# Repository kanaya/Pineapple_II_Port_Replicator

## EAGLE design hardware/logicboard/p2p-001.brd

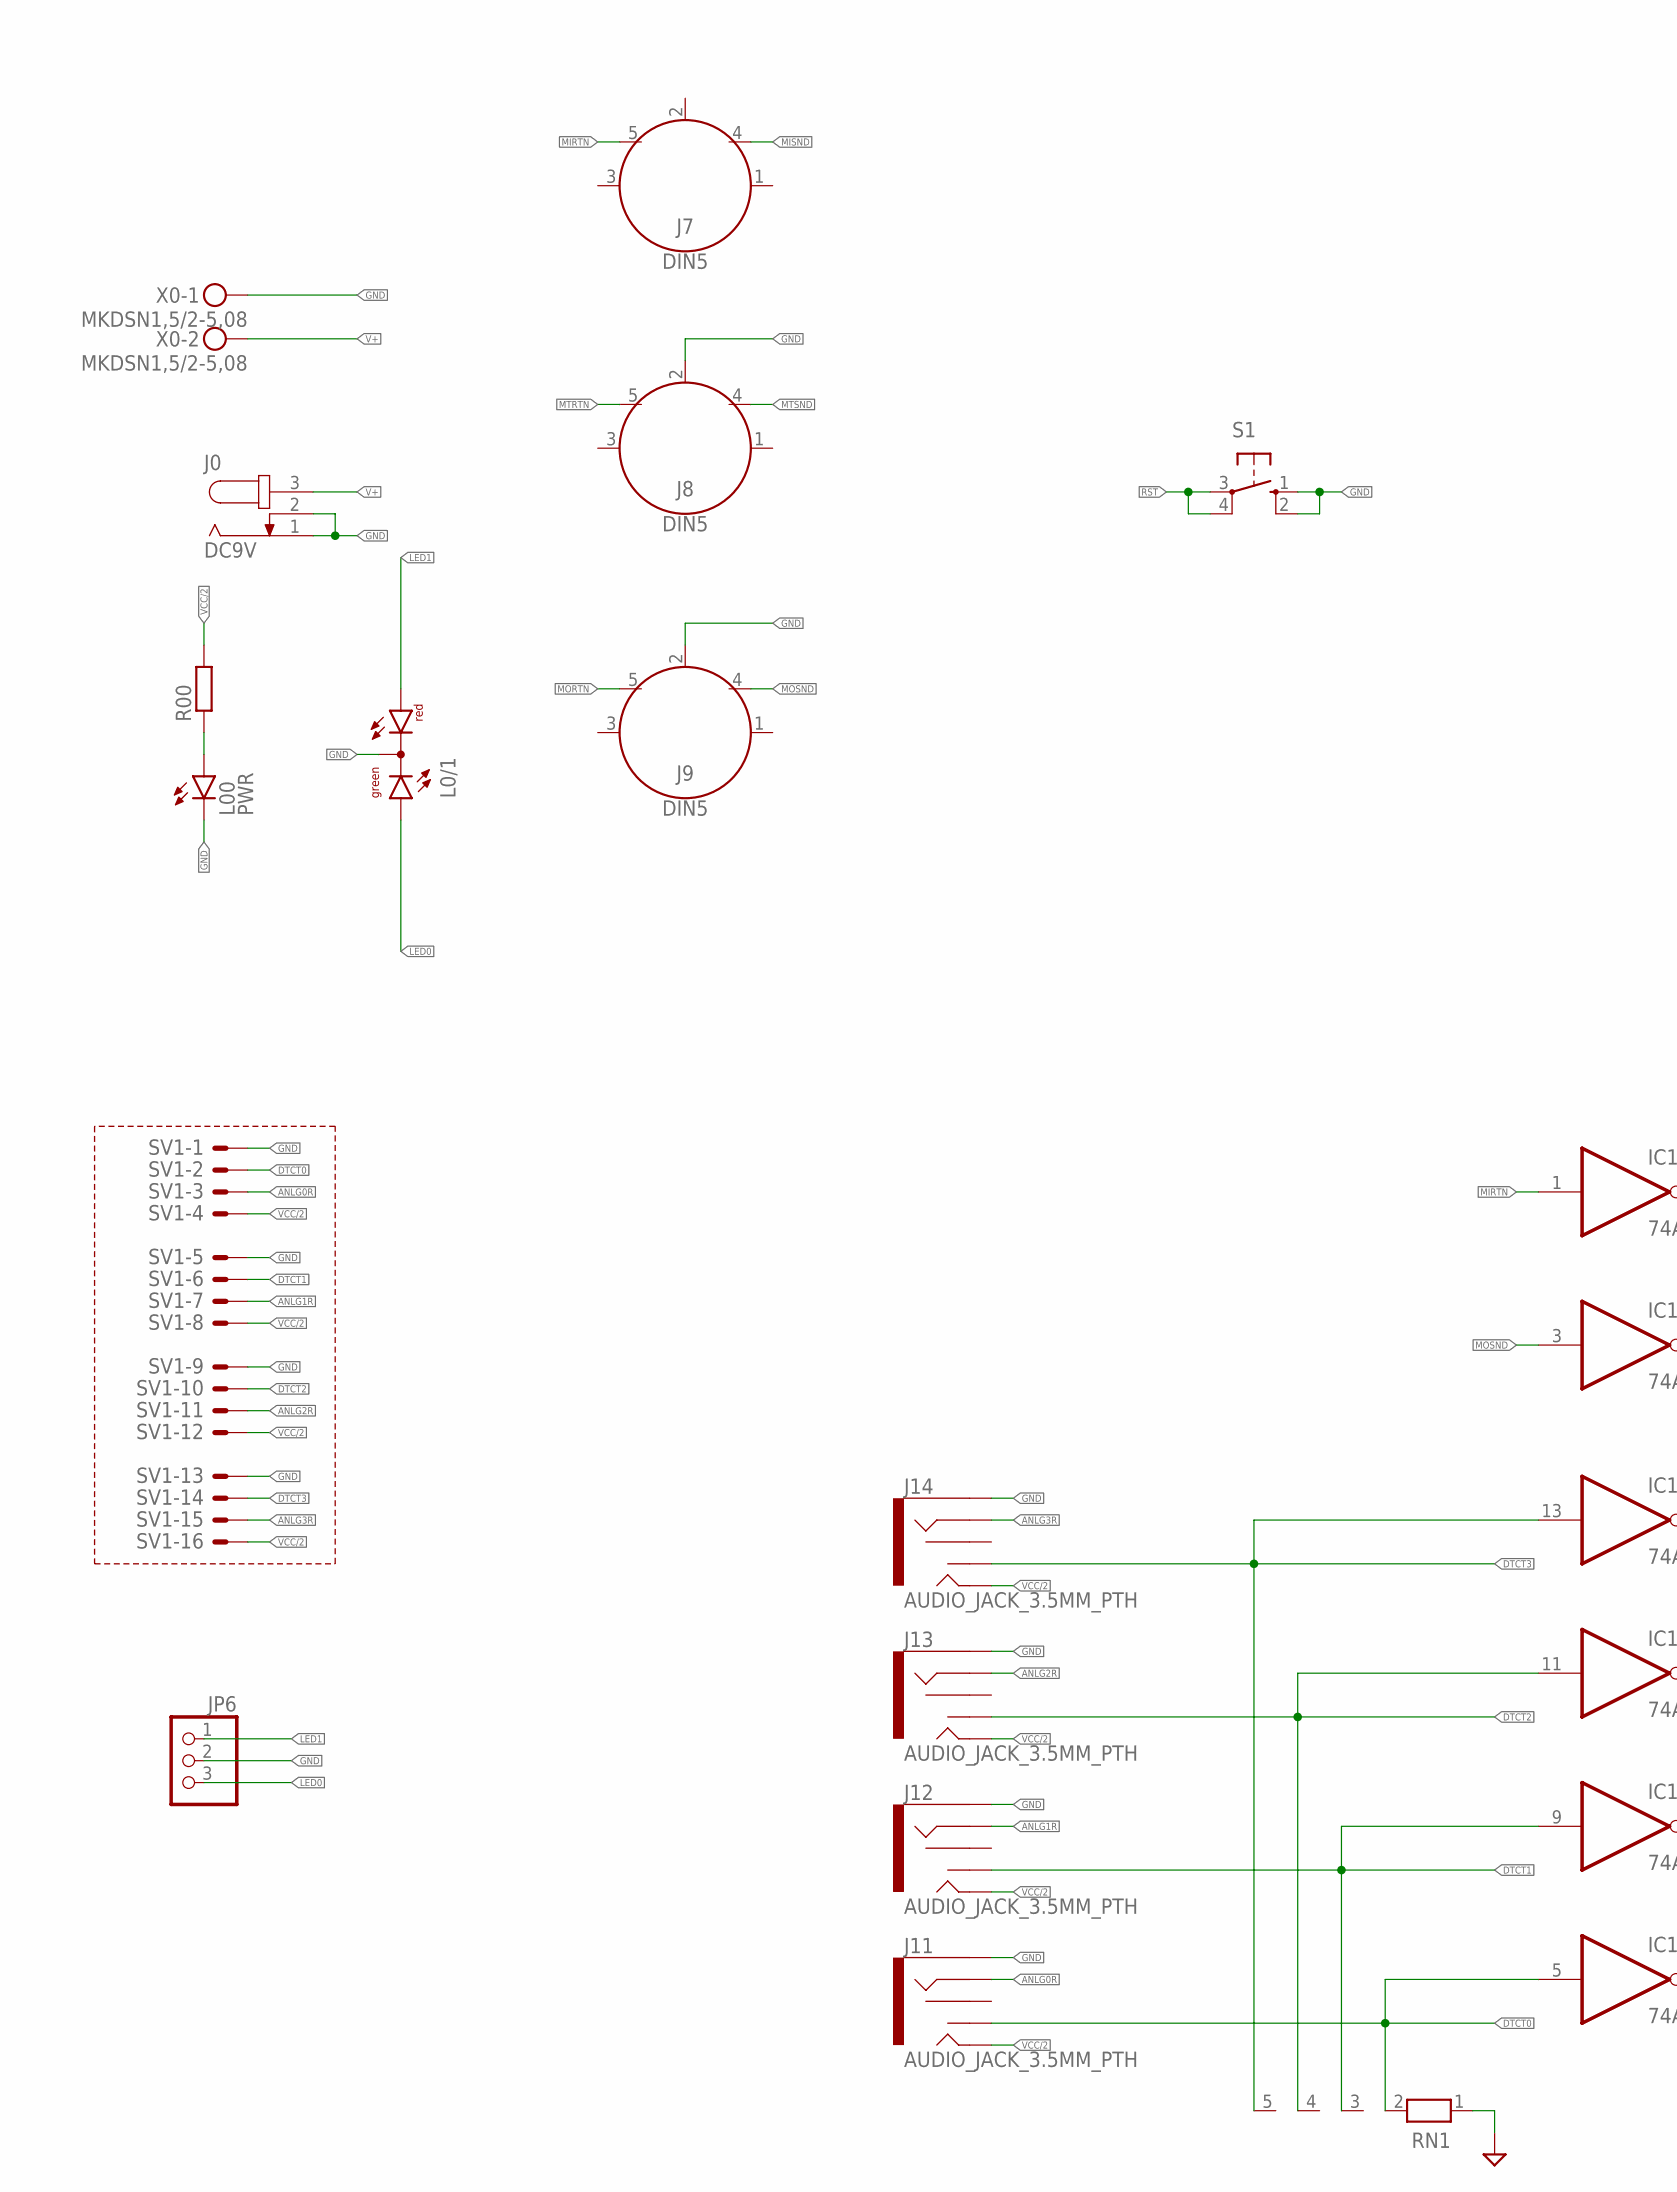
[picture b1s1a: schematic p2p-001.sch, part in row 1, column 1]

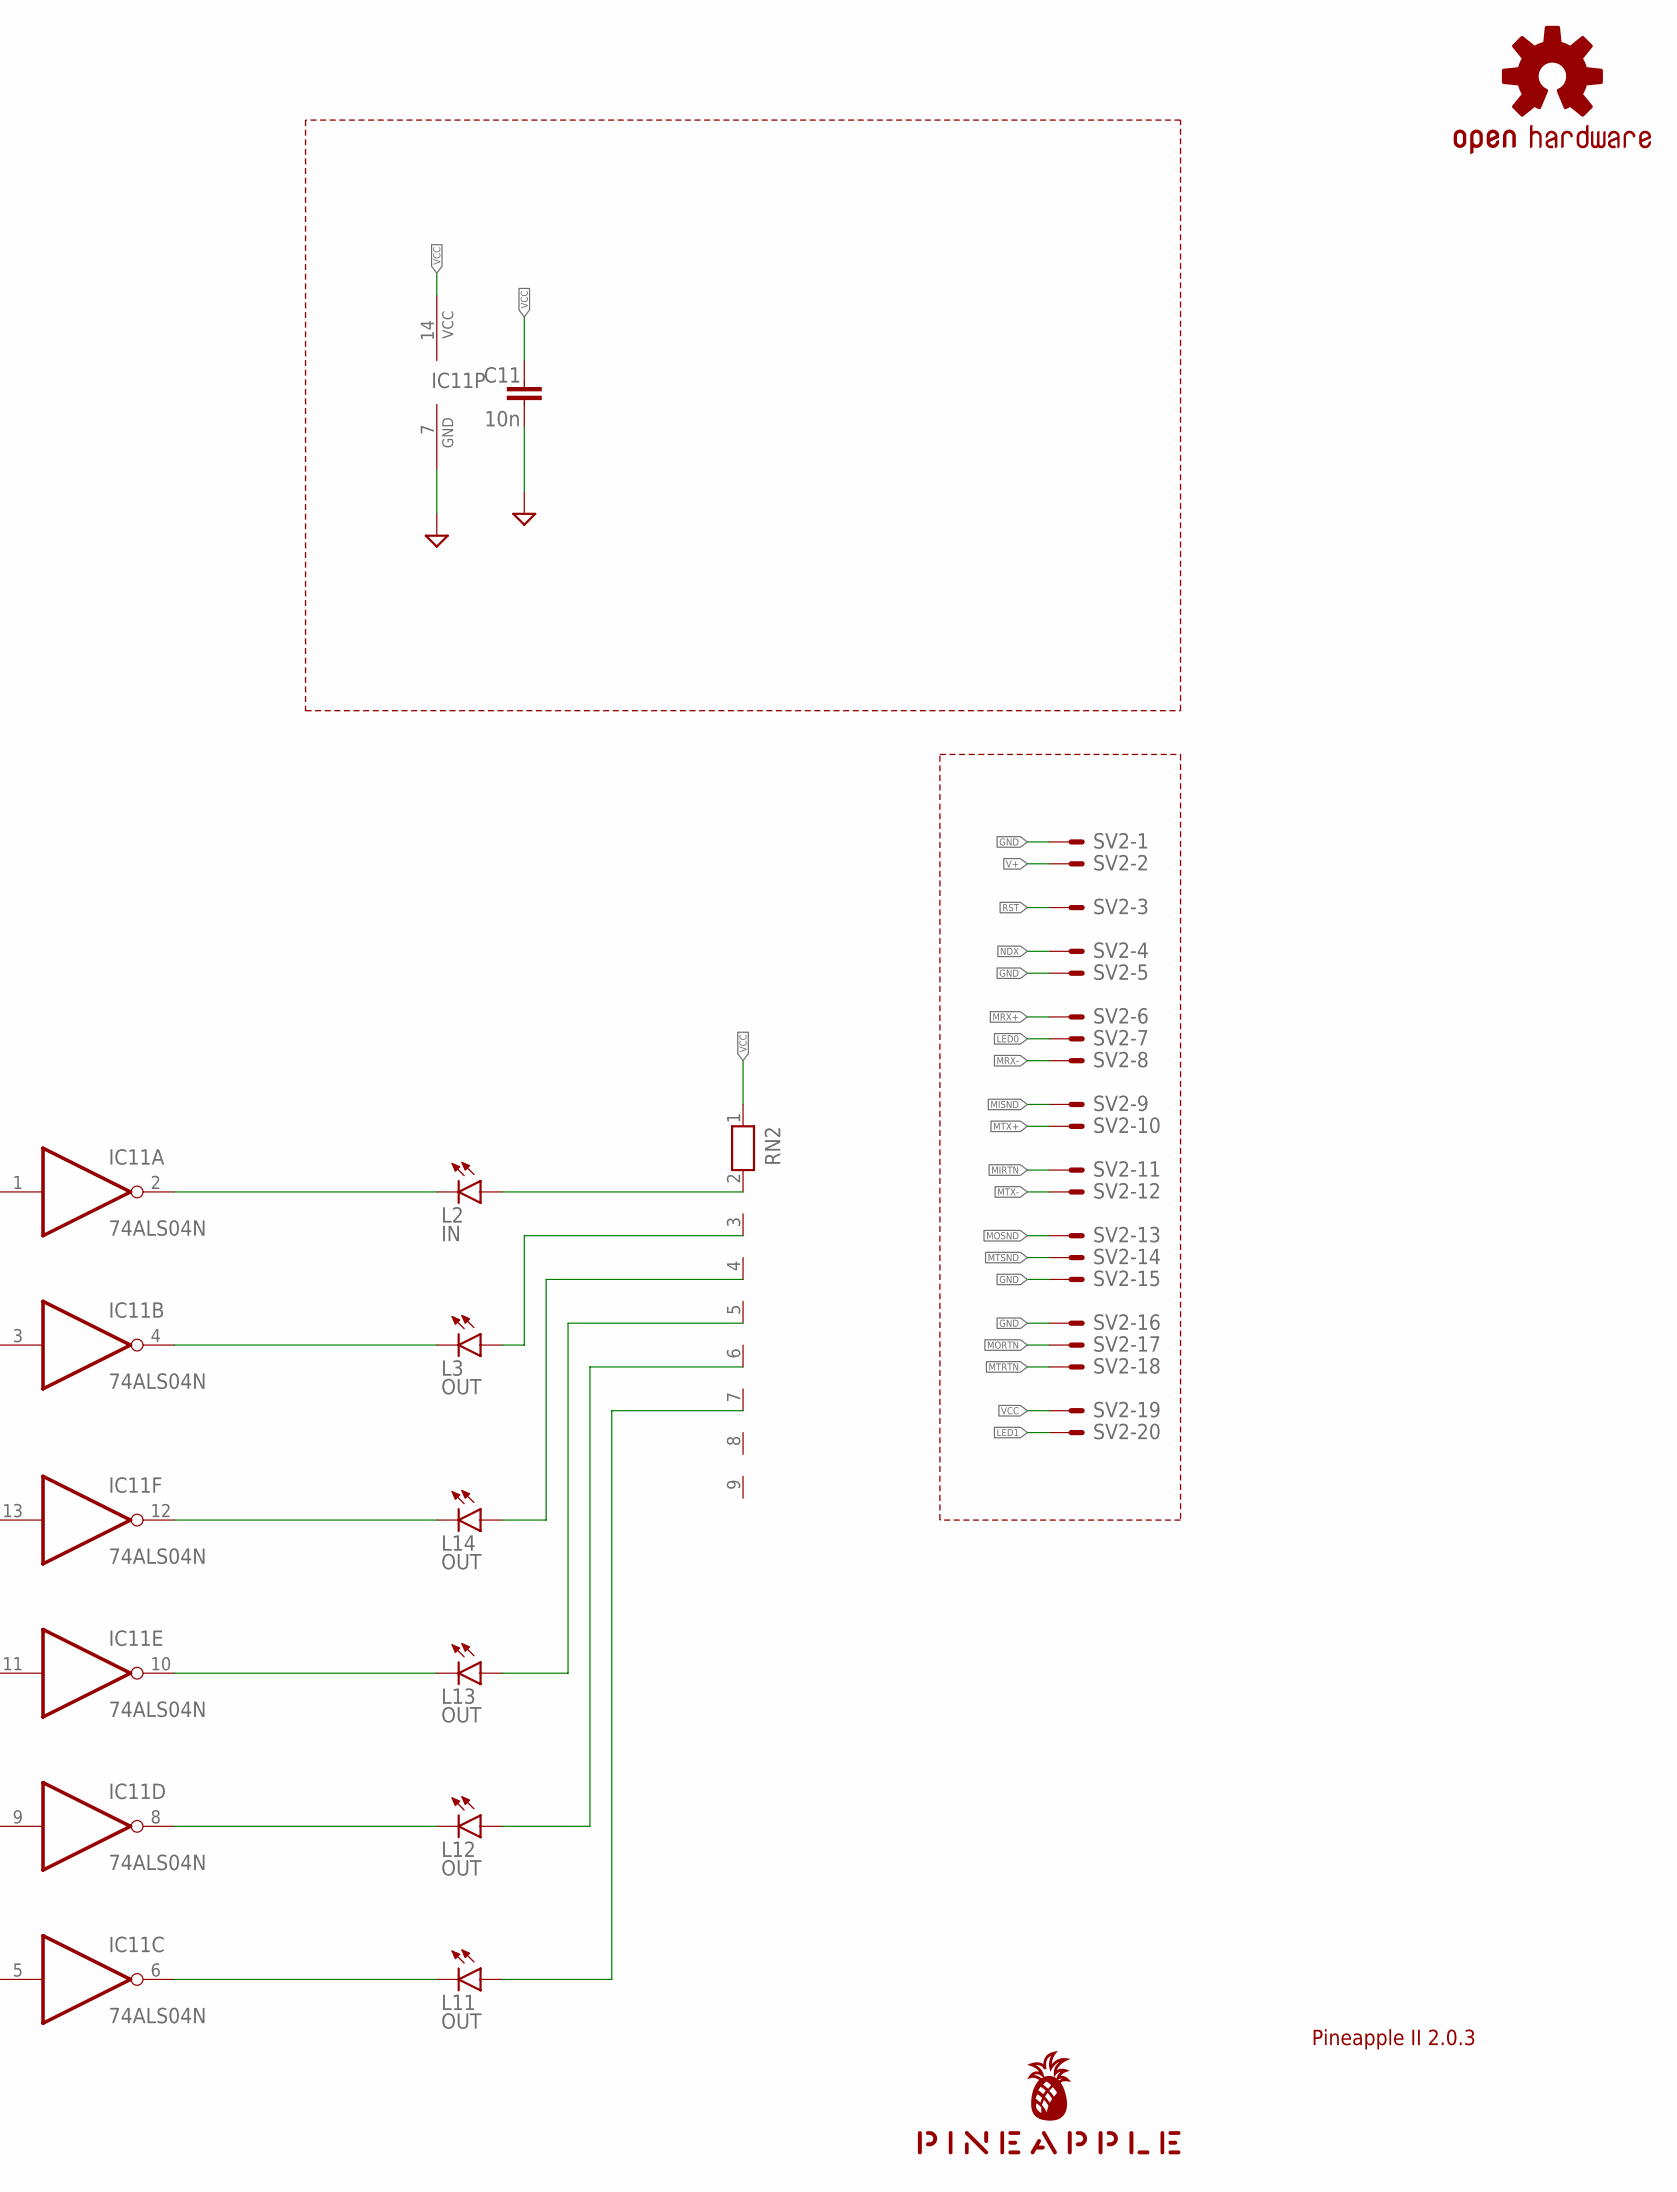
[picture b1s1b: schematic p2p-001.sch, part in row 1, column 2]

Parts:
C11: 10n; C025-024X044
IC11: 74ALS04N; DIL14
J0: DC9V; SPC4077
J7, J8, J9: DIN5; DIN5-RA-PTH
J11, J12, J13, J14: AUDIO_JACK_3.5MM_PTH; AUDIO-JACK
JP6: PINHD-1X3; 1X03
L00: PWR; LED3MM
L0/1: DUOLED-RG-C; DUOLED-C-5MM
L2: IN; LED3MM
L3, L11, L12, L13, L14: OUT; LED3MM
LOGO1: OSHW-LOGOS-COPPER; OSHW-LOGO-S_COPPER
R00: R-EU_0204/5; 0204/5
RN1: RN04; RN-5
RN2: RN08; RN-9
S1: 10-XX; B3F-10XX
SV1: ML16LE; ML16L
SV2: ML20LE; ML20L
U$1: PINEAPPLE450_SILK
X0: MKDSN1,5/2-5,08

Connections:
ANLG0R: J11.RING, SV1.3
ANLG1R: J12.RING, SV1.7
ANLG2R: J13.RING, SV1.11
ANLG3R: J14.RING, SV1.15
DTCT0: IC11.5 (I), J11.TSH, RN1.2, SV1.2
DTCT1: IC11.9 (I), J12.TSH, RN1.3, SV1.6
DTCT2: IC11.11 (I), J13.TSH, RN1.4, SV1.10
DTCT3: IC11.13 (I), J14.TSH, RN1.5, SV1.14
GND: C11.2, IC11.7 (GND), J0.1, J0.2, J8.2, J9.2, J11.SLEEVE, J12.SLEEVE, J13.SLEEVE, J14.SLEEVE, JP6.2, L00.K (C), L0/1.C, RN1.1, S1.1 (S), S1.2 (S1), SV1.1, SV1.5, SV1.9, SV1.13, SV2.1, SV2.5, SV2.15, SV2.16, X0.1
LED0: JP6.3, L0/1.AX (AG), SV2.7
LED1: JP6.1, L0/1.AR, SV2.20
LEDPWR: L00.A, R00.1
MIRTN: IC11.1 (I), J7.5, SV2.11
MISND: J7.4, SV2.9
MORTN: J9.5, SV2.17
MOSND: IC11.3 (I), J9.4, SV2.13
MRX+: SV2.6
MRX-: SV2.8
MTRTN: J8.5, SV2.18
MTSND: J8.4, SV2.14
MTX+: SV2.10
MTX-: SV2.12
unnamed: IC11.2 (O), L2.K (C)
unnamed: IC11.4 (O), L3.K (C)
unnamed: L2.A, RN2.2
unnamed: L3.A, RN2.3
unnamed: L14.A, RN2.4
unnamed: L13.A, RN2.5
unnamed: IC11.12 (O), L14.K (C)
unnamed: IC11.10 (O), L13.K (C)
unnamed: IC11.8 (O), L12.K (C)
unnamed: IC11.6 (O), L11.K (C)
unnamed: L12.A, RN2.6
unnamed: L11.A, RN2.7
NDX: SV2.4
RST: S1.3, S1.4 (P1), SV2.3
V+: J0.3, SV2.2, X0.2
VCC: C11.1, IC11.14 (VCC), RN2.1, SV2.19
VCC/2: J11.TIP, J12.TIP, J13.TIP, J14.TIP, R00.2, SV1.4, SV1.8, SV1.12, SV1.16

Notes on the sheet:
Pineapple II 2.0.3

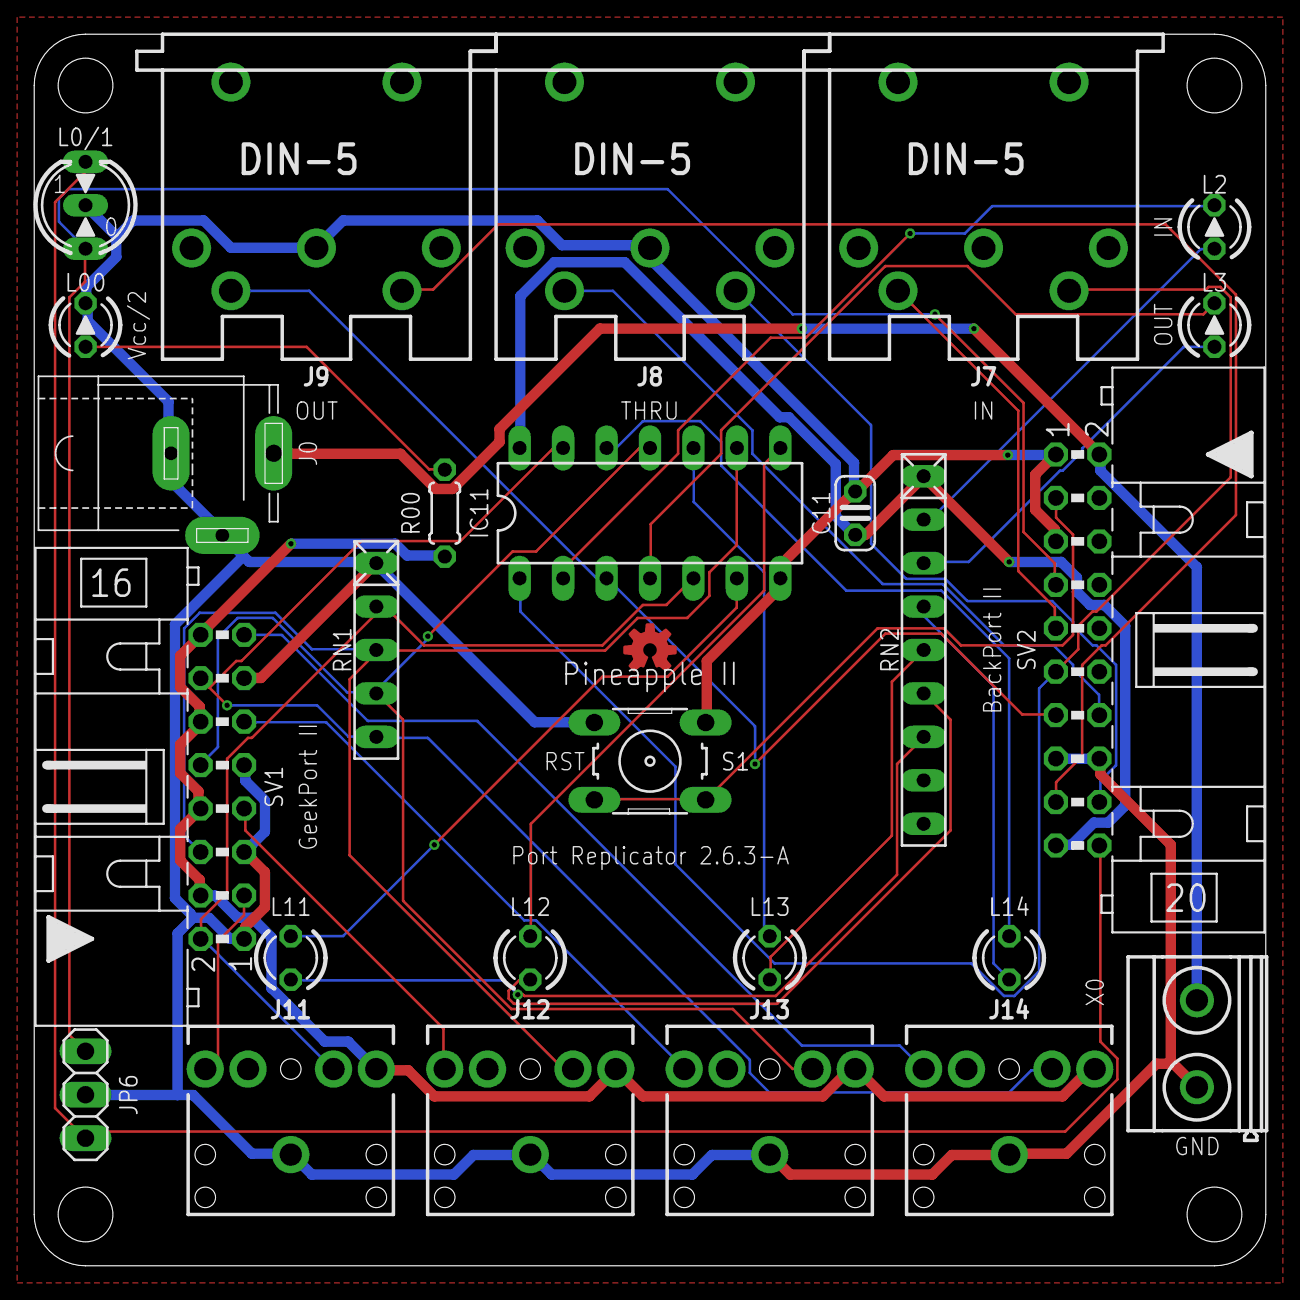
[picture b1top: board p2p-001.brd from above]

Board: 2 copper layers, 72.0 x 72.0 mm, 28 parts (1 on the bottom side), 34 nets.

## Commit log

2021-11-21 Copied schematic of Port Replicator of Pineapple II 2.4.0-B.
2021-11-28 Renumbered signals and parts.
2021-11-28 Renumbered parts.
2021-11-30 Adopted to GeekPort II and BackPort II.
2021-11-30 Renamed signals.
2022-08-17 Rename.
2022-08-18 Silk.
2022-08-18 Cloud work...
2022-08-18 GND pattern.

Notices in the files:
parts and their libraries:
SparkFun-Aesthetics: Licensing: Creative Commons ShareAlike 4.0 International - https://creativecommons.org/licenses/by-sa/4.0
